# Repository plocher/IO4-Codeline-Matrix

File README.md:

# IO4-Codeline-Matrix
## License: CERN Open Hardware Licence v1.2

IO4 interface for 2x LED Matrix displays (not for I2C expander ports)

2x 8x8 MAX7219 LED matrixes driven by the LedControl library

(replaced by [I2C-Codeline-Matrix](/pages/I2C-Codeline-Matrix.html))

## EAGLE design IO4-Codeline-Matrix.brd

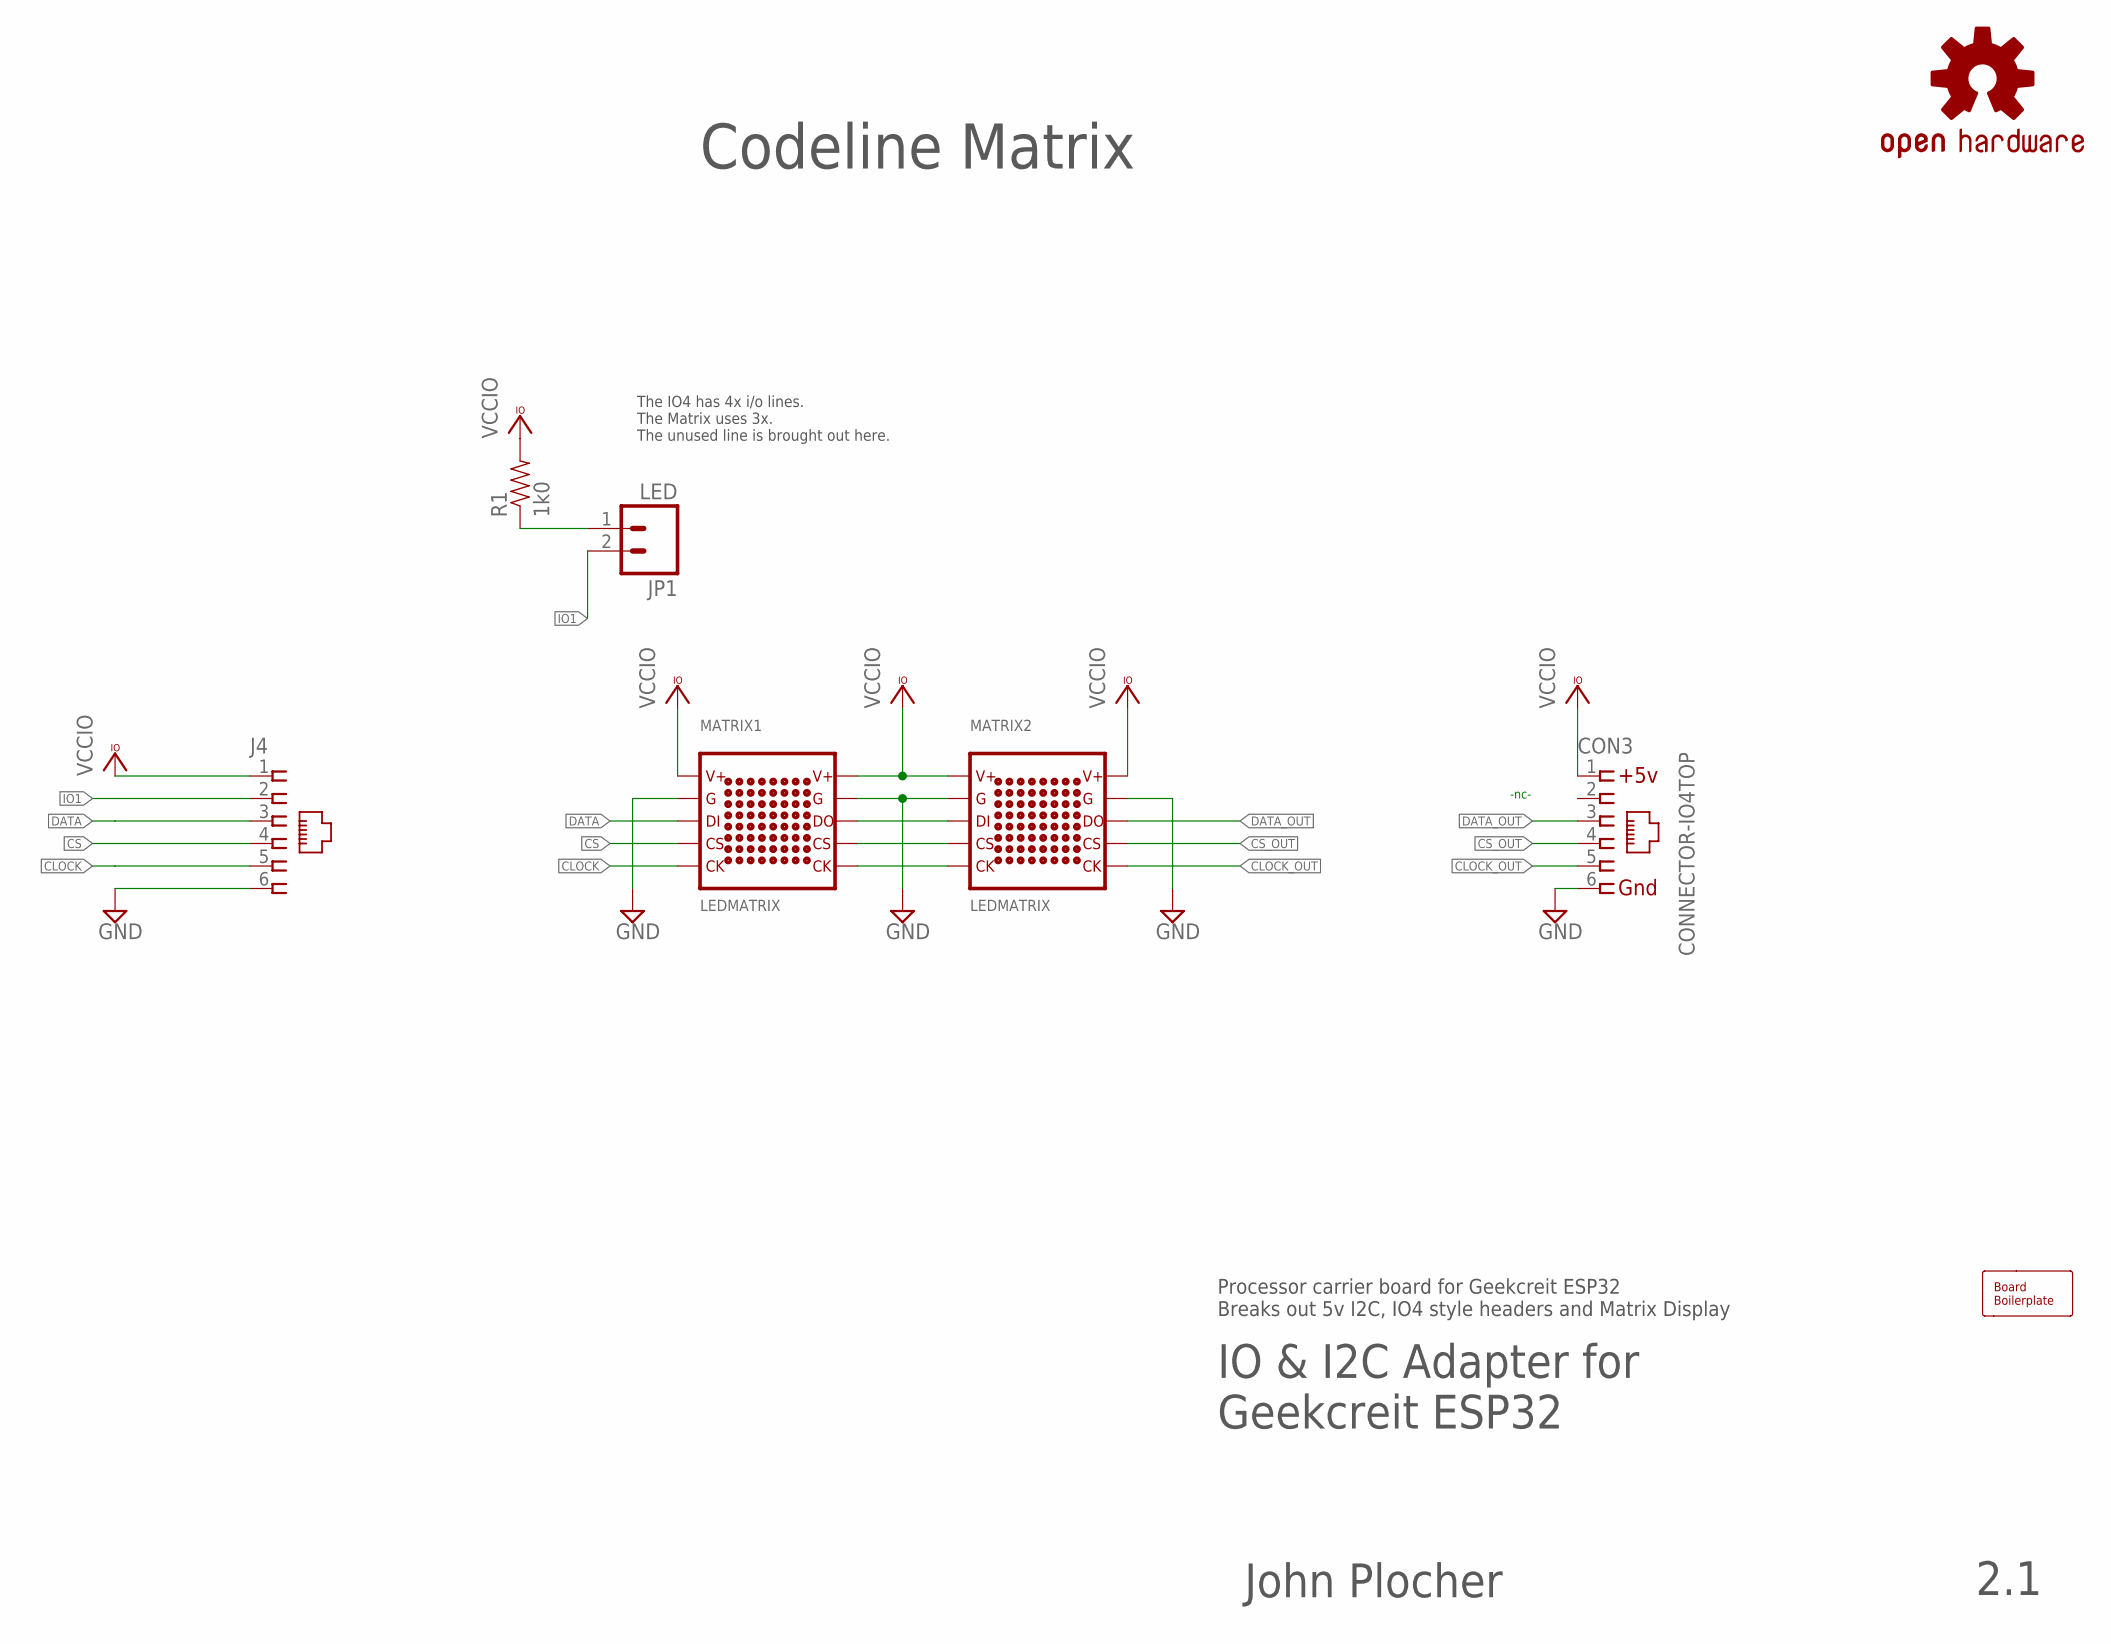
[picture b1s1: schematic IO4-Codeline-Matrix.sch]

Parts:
BOARD: BOARD80X150; BOARD-DINRAIL-3.17INX8CM
CON3: CONNECTOR-IO4TOP; RJ25-TOP
J4: CONNECTOR-RJ25-43860-2-MOLEX; RJ25-INVERTED
JP1: LED; 1X02_LOCK
MATRIX1, MATRIX2: LEDMATRIX
OSHW1: OSHW-LOGOL; OSHW-LOGO-L
R1: 1k0; AXIAL-0.4-RES

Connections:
CLOCK: J4.5, MATRIX1.CLK@1 (CLK)
CLOCK_OUT: CON3.5, MATRIX2.CLK@2 (CLK)
CS: J4.4, MATRIX1.CS@1 (CS)
CS_OUT: CON3.4, MATRIX2.CS@2 (CS)
DATA: J4.3, MATRIX1.DI (DIN)
DATA_OUT: CON3.3, MATRIX2.DO (DOUT)
GND: CON3.6, J4.6, MATRIX1.G@1 (G), MATRIX1.G@2 (G), MATRIX2.G@1 (G), MATRIX2.G@2 (G)
IO1: J4.2, JP1.2
unnamed: JP1.1, R1.P$1 (1)
unnamed: MATRIX1.DO (DOUT), MATRIX2.DI (DIN)
unnamed: MATRIX1.CS@2 (CS), MATRIX2.CS@1 (CS)
unnamed: MATRIX1.CLK@2 (CLK), MATRIX2.CLK@1 (CLK)
VCCIO: CON3.1, J4.1, MATRIX1.V+@1 (V+), MATRIX1.V+@2 (V+), MATRIX2.V+@1 (V+), MATRIX2.V+@2 (V+), R1.P$2 (2)

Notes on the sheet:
IO & I2C Adapter for Geekcreit ESP32
John Plocher
2.1
Processor carrier board for Geekcreit ESP32 Breaks out 5v I2C, IO4 style headers and Matrix Display
Codeline Matrix
-nc-
The IO4 has 4x i/o lines. The Matrix uses 3x. The unused line is brought out here.

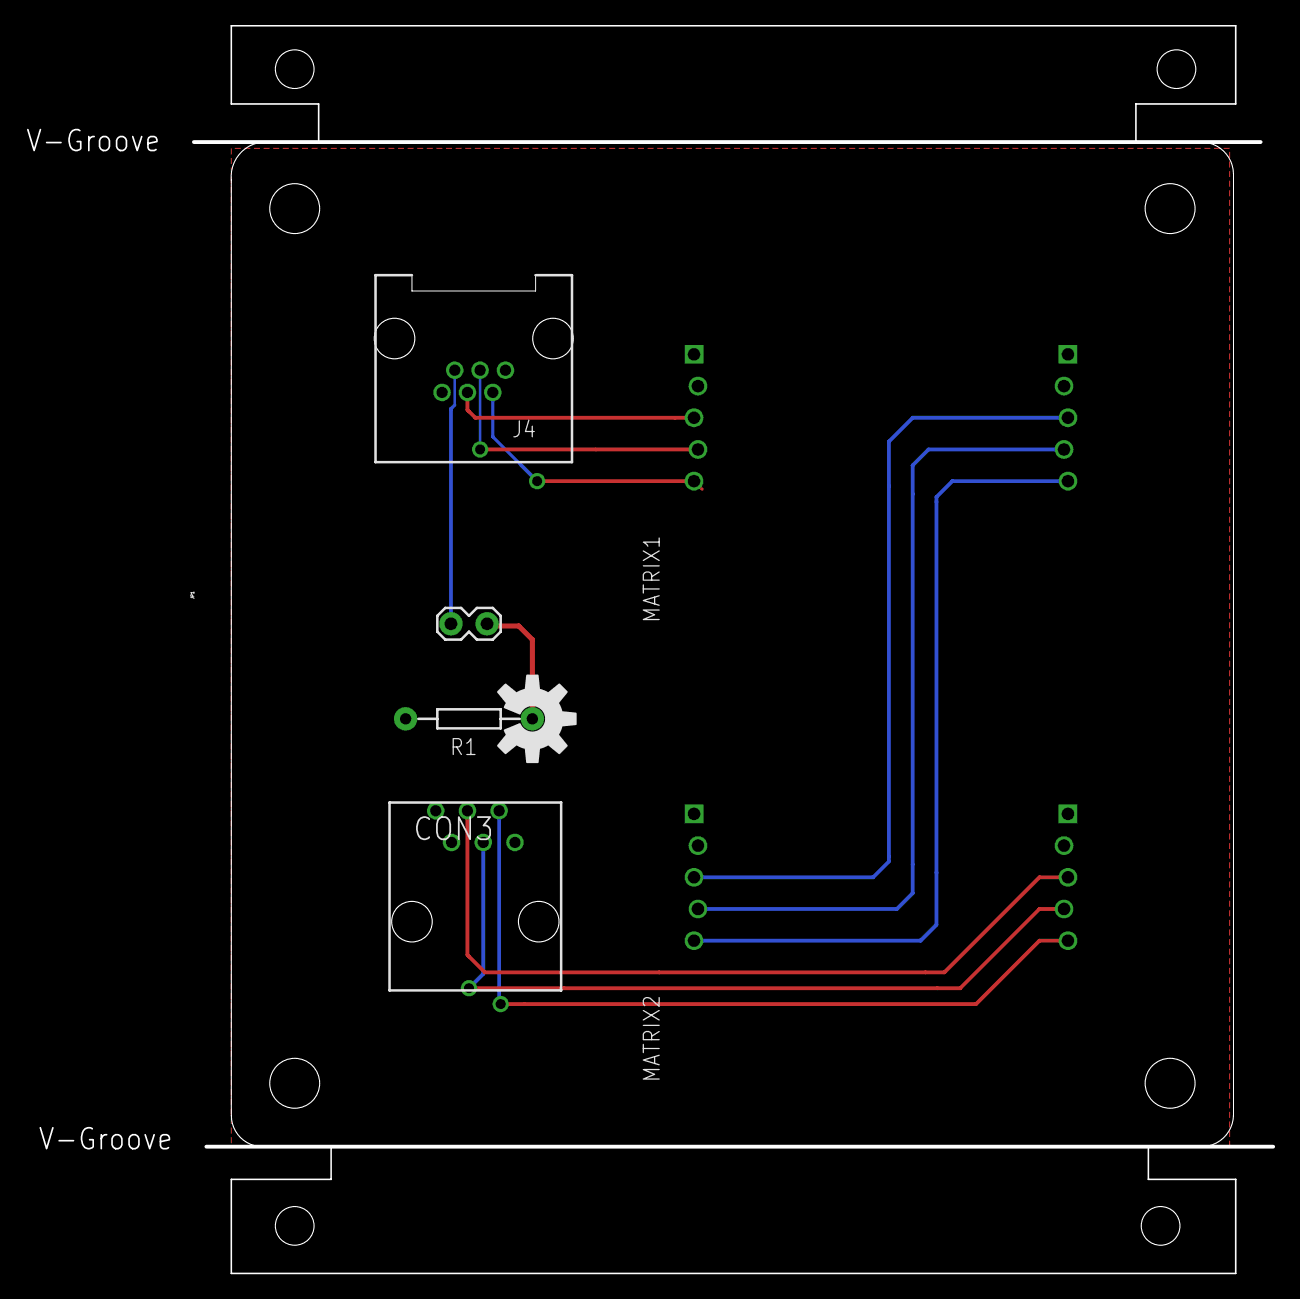
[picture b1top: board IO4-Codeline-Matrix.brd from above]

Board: 2 copper layers, 99.9 x 99.8 mm, 8 parts (0 on the bottom side), 13 nets.

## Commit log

2019-12-09 added graphic
2020-05-04 updated tags
2020-09-19 Obsolete

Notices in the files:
parts and their libraries:
SparkFun-Connectors: Licensing: CC v3.0 Share-Alike You are welcome to use this library for commercial purposes.
